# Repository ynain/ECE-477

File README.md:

View this project on [CADLAB.io](https://cadlab.io/project/1601). 

# ECE-477

The Code Composer Studio project folder is msp432/

application.py, bluetoothtest.py, src/pi_run.py, src/comp_run.py, and src/helpers.py and their dependencies should be the main files used in this project, and are the recommended ones for inspection, if you're looking to skip over test files and folders we used while figuring things out.
src/alt_trials/ should hold the files necessary for user registration and some example strucutre for what was used for this semester's project.

This project relies on Python 3.5 or above to work properly. Furthermore, DLIB, OpenCV, face_recognition, and several other PIP packages are required for download before this will run properly. Additional packages are required for a Raspberry Pi. For our conventience during initial testing, a discovered wheel build for Tensorflow on a Raspberry Pi was added for easy distrobution among our prototyping devices. It was offered up on a forum that we came across as we tried to build Tensorflow on a Pi from source.

Running application.py should detect whether on a Pi or Ubuntu, and this project isn't promised to work outside of those two environments. This also requires an MSP432 to be flashed with the code in  the msp432 Code Composer Studio project folder, and the EAGLE folder has some of our EAGLE source files, though at the writing of this document it is unknown if they're the latest versions.

This was a project that didn't get finalized to a manufacturing or distrobution setting, so we cannot promise that all of the board population components and project requirements are included in this GitHub.

Lastly, THIS SHOULD NOT BE USED FOR HIGH-SECURITY PURPOSES
Facial recognition has a few ways it can be easily fooled, and the accuracy of this network wasn't fully stress tested on edge cases (twins, close family resemblance, holding a photo up to the camera of a registered user, etc). If you'd like to use this project, it is recommended for personal interest projects at best, as it'd need large additions to become more realistically secure.

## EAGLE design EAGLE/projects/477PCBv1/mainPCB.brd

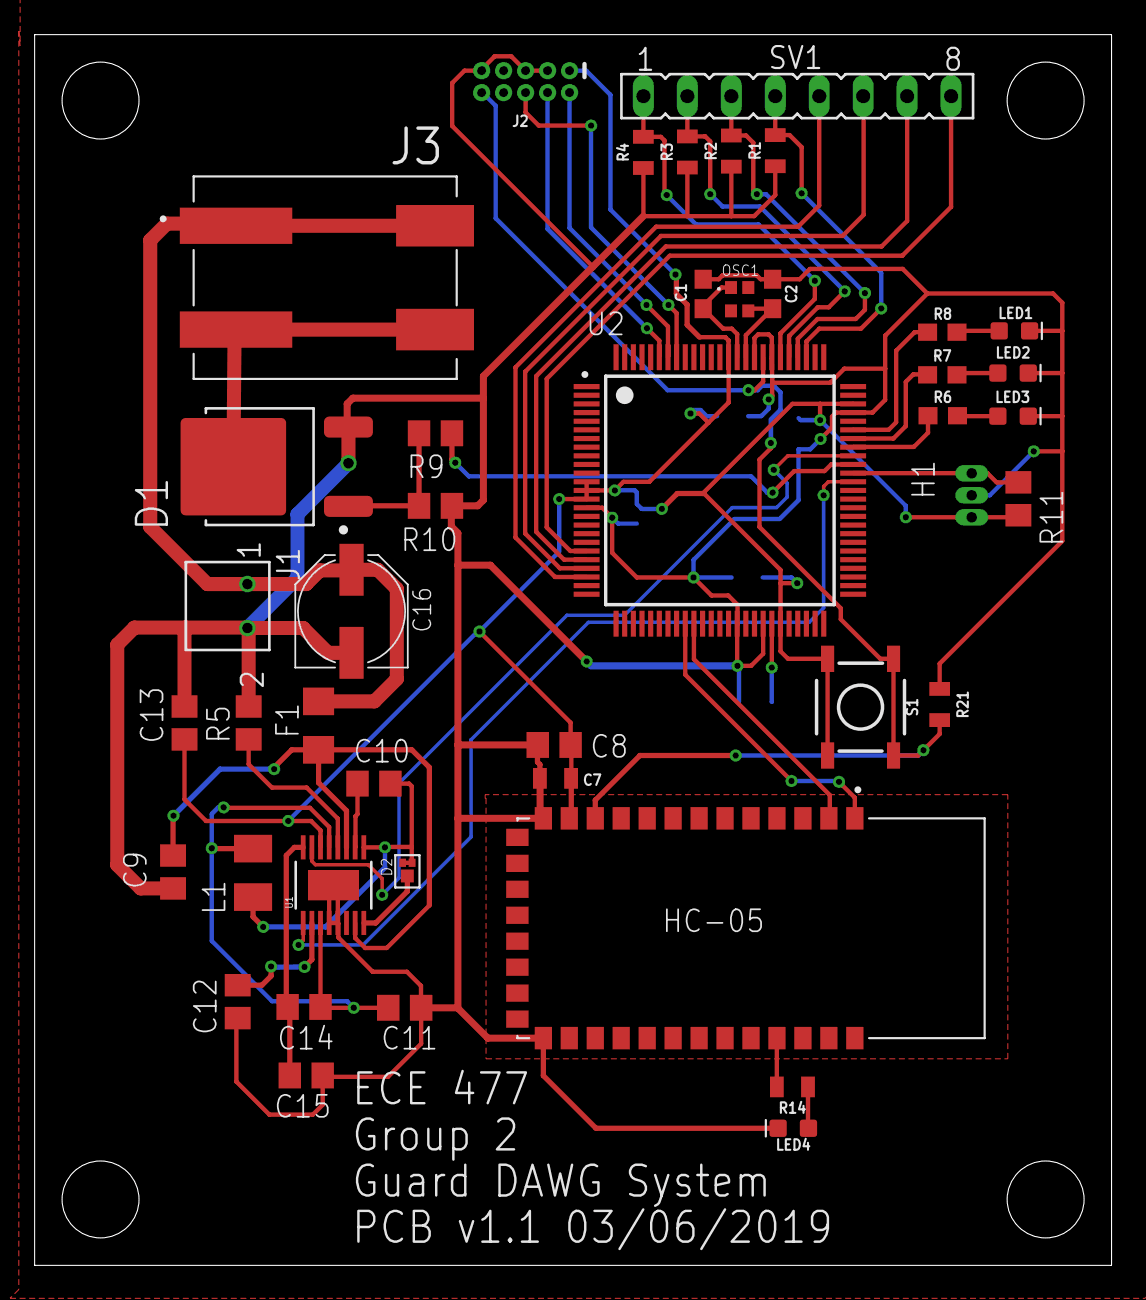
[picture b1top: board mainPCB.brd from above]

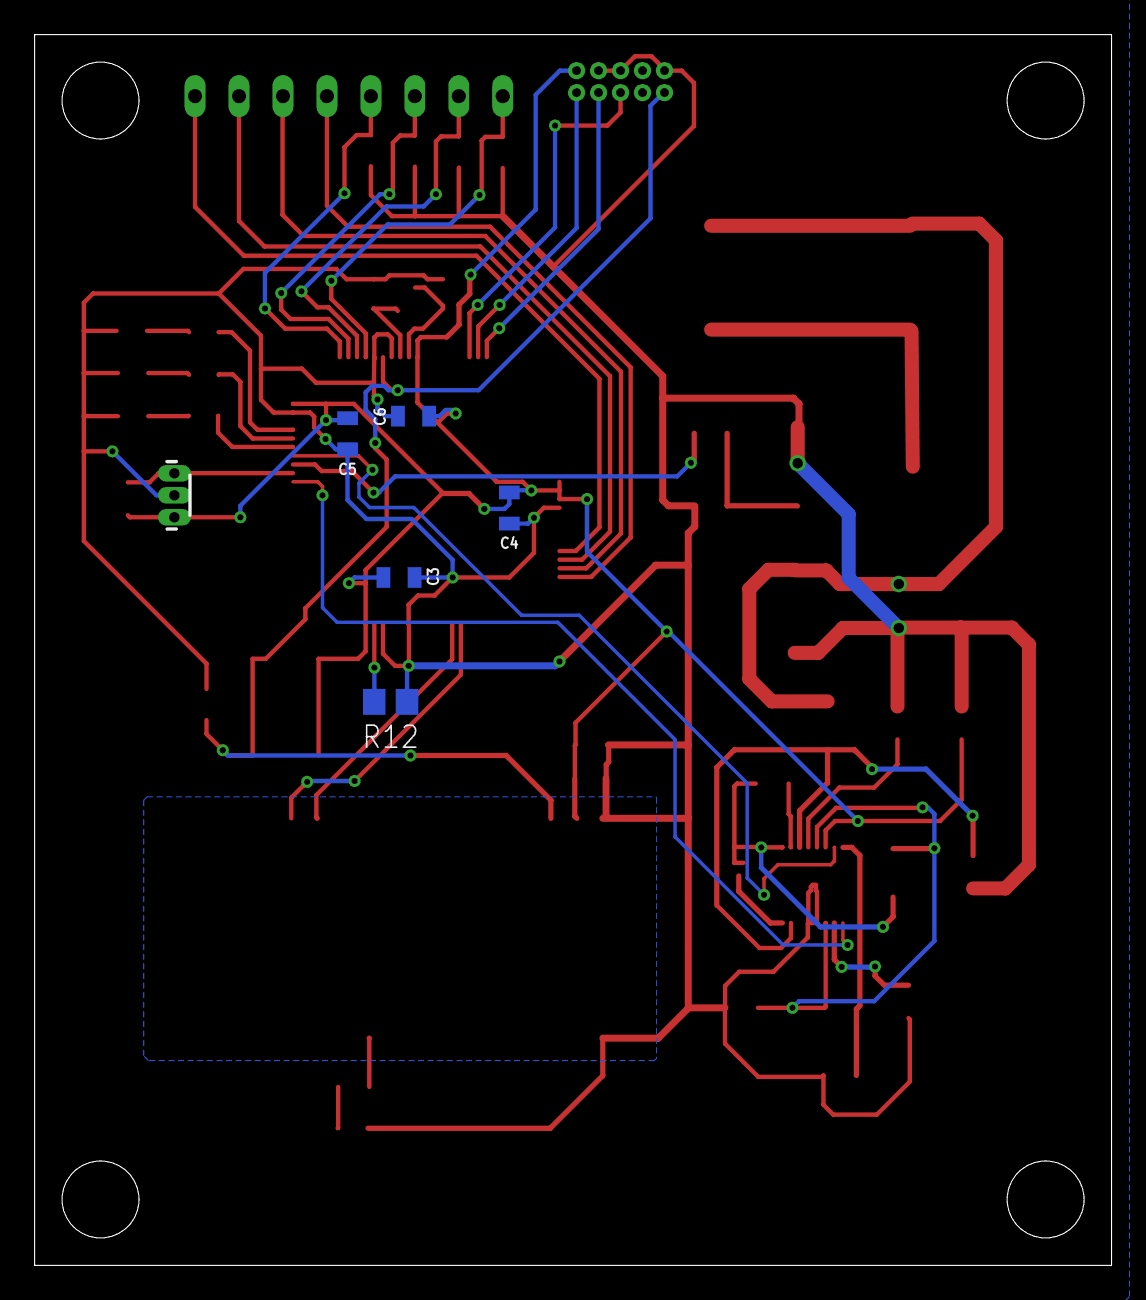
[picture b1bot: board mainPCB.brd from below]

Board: 2 copper layers, 62.2 x 71.1 mm, 48 parts (6 on the bottom side), 42 nets.

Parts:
C1, C2: 22pF; 0603
C3, C4, C5, C6: 0805
C7: 0.1UF-0805-100V-10%; 0805
C8: 0.01u; C0805
C9: 4.7uF; C0805
C10: 0.22uF; C0805
C11: 15uF; C0805
C12, C13: 10pF; C0805
C14: 10k; R0805
C15: 5.76k; R0805
C16: 100uF; PANASONIC_D
D1: RFD3055LESM9A; DPAK229P990X239-4N
D2: SBR1U40LP; 3-XDFN
F1: C1Q3751206; C1206
H1: HES; SIP3-UA
HC-05: HC-05; XCVR_HC-05
J1: 640455-2; 2-PIN_CONNECTOR
J2: CORTEX_DEBUG_PTH; 2X5-PTH-1.27MM
J3: 2061-602/998-404; WAGO_2061-602/998-404
L1: 10uH; L3225M
LED1: BLUE; LED-0603
LED2: Red; LED-0603
LED3: GREEN; LED-0603
LED4: RED; LED-0603
OSC1: XRCGB48M000F0L00R0; XTAL_XRCGB24M000F0L00R0
R1, R2, R3, R4, R21: 10k; 0805
R5: 95.3k; R0805
R6, R7, R8: 2.0k; 0603
R9: 24k; R0805
R10: 1M; R0805
R11: 10k; R0805
R12: 91k-0.1%; R0805
R14: 2.0KOHM; 0805
S1: SWITCH; TACTILE_SWITCH_SMD_5.2MM
SV1: FE08
U1: LT3668EMSEPBF; MSOP-16_MSE
U2: MSP432P401RIPZR; QFP50P1600X1600X160-100N

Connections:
3.3V: C3.1, C4.1, C5.1, C6.1, C7.1, C8.1, C13.1, H1.1, HC-05.12, J2.1, R11.2, S1.3, S1.4, U1.6, U2.12, U2.13, U2.14, U2.45, U2.73, U2.87
ADJ2: U1.9, U2.64
ADJ3: U1.7, U2.67
BLED: R8.2, U2.70
BOOST: C10.1, U1.2
COL1: R1.2, SV1.4, U2.78
COL2: R2.2, SV1.3, U2.79
COL3: R3.2, SV1.2, U2.80
COL4: R4.2, SV1.1, U2.81
DA: D2.1, U1.16
FB1: C14.1, C15.2, U1.8
GLED: R6.2, U2.68
GND: C1.1, C2.1, C3.2, C4.2, C5.2, C6.2, C7.2, C8.2, C9.2, C11.2, C12.2, C13.2, C15.1, C16.-, D1.3, H1.2, HC-05.13, HC-05.22, J1.2, J2.3, J2.5, J2.9, LED1.C, LED2.C, LED3.C, LED4.C, R1.1, R2.1, R3.1, R4.1, R5.1, R10.1, R12.2, R21.2, U1.12, U1.13, U1.17, U2.15, U2.40, U2.43, U2.72, U2.82, U2.84
HALL: H1.3, R11.1, U2.65
HFX_IN: C1.2, OSC1.1, U2.86
HFX_OUT: C2.2, OSC1.3, U2.85
IN1: C9.1, F1.2, U1.3, U1.15
IN2/3: C11.1, C14.2, L1.2, U1.5, U1.11
unnamed: D1.1, R9.2, R10.2
unnamed: D1.4, J3.2_1, J3.2_2
unnamed: LED4.A, R14.1
unnamed: LED3.A, R6.1
unnamed: LED2.A, R7.1
unnamed: LED1.A, R8.1
unnamed: R12.1, U2.44
unnamed: HC-05.31, R14.2
OUT2: C12.1, U1.10
PUSH: R9.1, U2.66
RESET: HC-05.11, J2.10, R21.1, S1.1, S1.2, U2.83
RLED: R7.2, U2.69
ROW1: SV1.8, U2.20
ROW2: SV1.7, U2.21
ROW3: SV1.6, U2.22
ROW4: SV1.5, U2.23
RT: R5.2, U1.4
RX_D: HC-05.2, U2.35
SW: C10.2, D2.2, D2.3, L1.1, U1.1
SWDCLK: J2.4, U2.95
SWDIO: J2.2, U2.94
SWO: J2.6, U2.93
TX_D: HC-05.1, U2.34
VCC_1: C16.+, F1.1, J1.1, J3.1_1, J3.1_2

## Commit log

2019-01-13 Added my name
2019-01-13 change
2019-01-17 Python code for early camera functionality
2019-01-26 Pi code for coding with pi is working so far
2019-01-26 Able to connect to Pi, as long as HOST is Pi's own IP Address
2019-01-26 Tensorflow is bae (Current raspbian version, Python 3.5)
2019-01-26 Getting to streaming potential
2019-01-27 fps update
2019-01-27 Got streaming working from example, threading may be needed for 4fps
2019-01-27 testing threading for speed increase of the process
2019-01-27 This file status setting for thread_client.py got 13 images to send in 3 seconds for 4.14fps, and 9 images in 2s for 4.05 fps. Likely the setting we'll use if we want to hit 4fps
2019-01-27 Bluetooth inspected, files restructured
2019-01-27 editing to let the computer be the client... and understanding socket connections meanwhile
2019-01-27 Fixing reference errors
2019-01-27 Got laptop to pi working, need direct network connection for now
2019-01-27 Trying to ignore subdirectory images
2019-01-28 Giving credit to the source
2019-01-28 Giving credit to the source enabling wifi hotspotting for the Pi. And also ignoring frames loaded by this script.
2019-01-28 basic uart example
2019-01-30 Trying to organize/understand socket files
2019-01-30 referencing error... also more errors... will fix later
2019-01-30 more referencing fun
2019-01-31 Threads close fully now
2019-01-31 Trying to organize the file a bit more
2019-01-31 Probably a lost cause
2019-01-31 Referencing
2019-01-31 Ignoring more test files
2019-01-31 Works, but is much slower
2019-01-31 Trying unthreaded
2019-01-31 removing false redefine
2019-01-31 Moref fererencing errors
2019-01-31 Specified length to read, for redundancy
2019-01-31 synchronous sending works
2019-02-01 Ignoring venv environment
2019-02-01 Setting up facenet
2019-02-02 Should have been a directory name
2019-02-03 Trying to combine things into an application
2019-02-03 Computer is the server, pi is the client, process flow makes more sense that way
2019-02-03 Starting application process
2019-02-03 Overall application for Pi and Computer
2019-02-03 Aligning imports with Pi side
2019-02-03 Faces are able to be piped in and recognized, no faces in frame is caught, and FaceNet automatically picks out the largest face in the image? Need to suppress the terminal output if we're going to co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
2019-02-03 Both Pi and Computer can run on application.py.
2019-02-03 Python 3.5+ enforced
2019-02-04 Getting face_recognition working, and saving encodings as we go
2019-02-04 Seems to work, fixing hanging pipe issue
2019-02-04 Fixing divide by 0 error
2019-02-04 Fixing bad pipe connection issues
2019-02-06 Starting to get code working
2019-02-06 Referencing apparently bad? Fixed 'frame' to 'face' variable
2019-02-06 Getting rid of face border
2019-02-06 Basics written, time to debug
2019-02-06 encoding formats attempt
2019-02-06 Message being written properly, pi needs to recieve it now
2019-02-06 Fixing enpoint close error
2019-02-06 connection issues too
2019-02-06 fixing packaging
2019-02-06 Finally receiving
2019-02-06 Pi is getting results! Needs cleaning though
2019-02-06 computer getting good message to pi now
2019-02-08 Added check in case npz file isn't present, also fixing frame/face variable error for the 16th time I swear, don't know why it's persisting
2019-02-10 Got Viki pulled in, saving the vector encodings
2019-02-10 Backlink to CADLAB.io has been added.
2019-02-10 Viki: got something to work
2019-02-13 Trying to get Bluetooth working... phone app receiver isn't working, but can find phone when manually scan bluetooth visible to it. HC-05 isn't ready to receive yet, so might need to hook up two pi's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
2019-02-14 Testing bluetooth with pi server
2019-02-14 Testing bluetooth with pi client
2019-02-14 Able to connect to the HC-05 with the hc05 and the sendmaybe.py files as is
2019-02-15 Fixing some minor comment styles, and removing unnecessary code
2019-02-17 Double checked that we're pulling the largest face out of the images
2019-02-17 Dammit Viki I hate this
2019-02-17 Viki doing stuff I had IPs kill me now
2019-02-17 Takes forever, but works... Why, Viki, why
2019-02-18 getting the msg, not sure how to stop it
2019-02-18 Hardcoded is easier
2019-02-18 Structuring the application
2019-02-18 Viki why do you leave empty code hanging on the Pi, I need to branch juggle...
2019-02-18 Making application structure
2019-02-18 Making old application file still runnable
2019-02-18 Small error with IP addresses
2019-02-18 Starting on the Pi side of the application, think there's an error from the old code remaking a connection every time something is to be sent
2019-02-19 Getting system checks and OS dependant dependencies pulled in
2019-02-19 Getting IP address set up for testing, and ignoring swap files from VIM
2019-02-19 Forgot to get the operating system register made
2019-02-19 Adding input sections
2019-02-19 Pi remade to work with connection files, rather than the default connection itself
2019-02-19 Filling in the needed functions for pi_run... now to debug and test
2019-02-19 Getting things into a try-catch statement
2019-02-19 Ignoring python compilation files
2019-02-19 Get rid of pyc files
2019-02-19 Moved two.py to bluetooth folder in src
2019-02-19 Works on everything except initial message? Still debugging
2019-02-19 Getting sockets to work... Flush. Everything.
2019-02-19 Computer end of getting socket to work
2019-02-19 Fixing default ip address
2019-02-20 Working on getting Bluetooth into the process
2019-02-20 More work on application status. Need to play with pi's for fun
2019-02-22 Trying a thing, didn't work
2019-02-22 Saving James
2019-03-01 Apparently doesn't work for the Pi
2019-03-01 No conflict
2019-03-01 Moving micro ccs folder to the GitHub
2019-03-03 Accepting weird message issues, going forward with application prototyping
2019-03-04 Updates to make application work, need testing
2019-03-04 Imaging Viki
2019-03-04 Fixed installs
2019-03-06 Got the application working with the current Micro 'state machine'
2019-03-06 Healthier error catching and close statements
2019-03-22 Saving current msp432 status, with STATE flag for HC-05 working
2019-03-22 Some logic to exit the process upon bluetooth connection disconnect
2019-03-22 Not sending signals if not connected
2019-03-22 Saving Evan's status
2019-03-22 Weird interrupt issue
2019-03-27 added some test code
2019-03-27 Trying to check why things aren't working... they were, but IP addresses are a bitch
2019-03-27 Minor changes for errors and exception logic
2019-03-28 PCBv1
    Original PCBv1 schematic/layout/gerbers
2019-03-28 Revert to "Not sending signals if not connected"
    This reverts commit 06c78371b09302636f16c74713acbd3d6e6c9776.
2019-03-28 Fixed some things
2019-03-29 fixing Ian's mess up
2019-03-31 Adding bluetooth test file
2019-03-31 Really need to make a dynamic way to get connection's IP address
2019-03-31 unfucking what Ian did
2019-04-01 Think includes are working now
2019-04-01 Builds now, should be roughly fixed...?
2019-04-01 keypad driver is alive.
2019-04-01 back to what we had
2019-04-01 Bluetooth test script works?
2019-04-01 Bluetooth script with password
2019-04-01 added some password logic, still buggy
2019-04-02 Keypad working again :)) - Evan
2019-04-02 Simple keypad lock/unlock sequence -E
2019-04-03 Password update
2019-04-03 Should have password pulled in
2019-04-03 Changing except level
2019-04-03 Was stuck on same signal
2019-04-03 in-lab commit, password logic works
2019-04-07 integrated keypad & hc-05
2019-04-07 works-ish
2019-04-08 neww
2019-04-14 Direct connection IP is good
2019-04-14 Application and bluetooth are good... I think
2019-04-14 Getting rid of the extra layer of try/catch fully
2019-04-15 keypad works!
2019-04-15 can change passcode now
2019-04-17 some changes made by Evan..?
2019-04-19 ready to check off BlueTooth PSSC
2019-04-19 First trial for getting the App PCB-run, and not laptop run
2019-04-21 cleaned some of the code up
2019-04-21 mac addr
2019-04-23 fixed small things
2019-04-23 print statements
2019-04-23 Code working from testing
2019-04-23 Computer doesn't need to rotate now
2019-04-24 some shit
2019-04-25 works
2019-04-28 Added a folder-creation capability to mapfaceEncodings.py
2019-04-29 Adding capability of image borders
2019-04-29 micro-fix merge conflict
2019-04-29 Final words
2019-04-29 More final words

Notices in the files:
parts and their libraries:
SparkFun-Capacitors: Licensing: Creative Commons ShareAlike 4.0 International - https://creativecommons.org/licenses/by-sa/4.0
